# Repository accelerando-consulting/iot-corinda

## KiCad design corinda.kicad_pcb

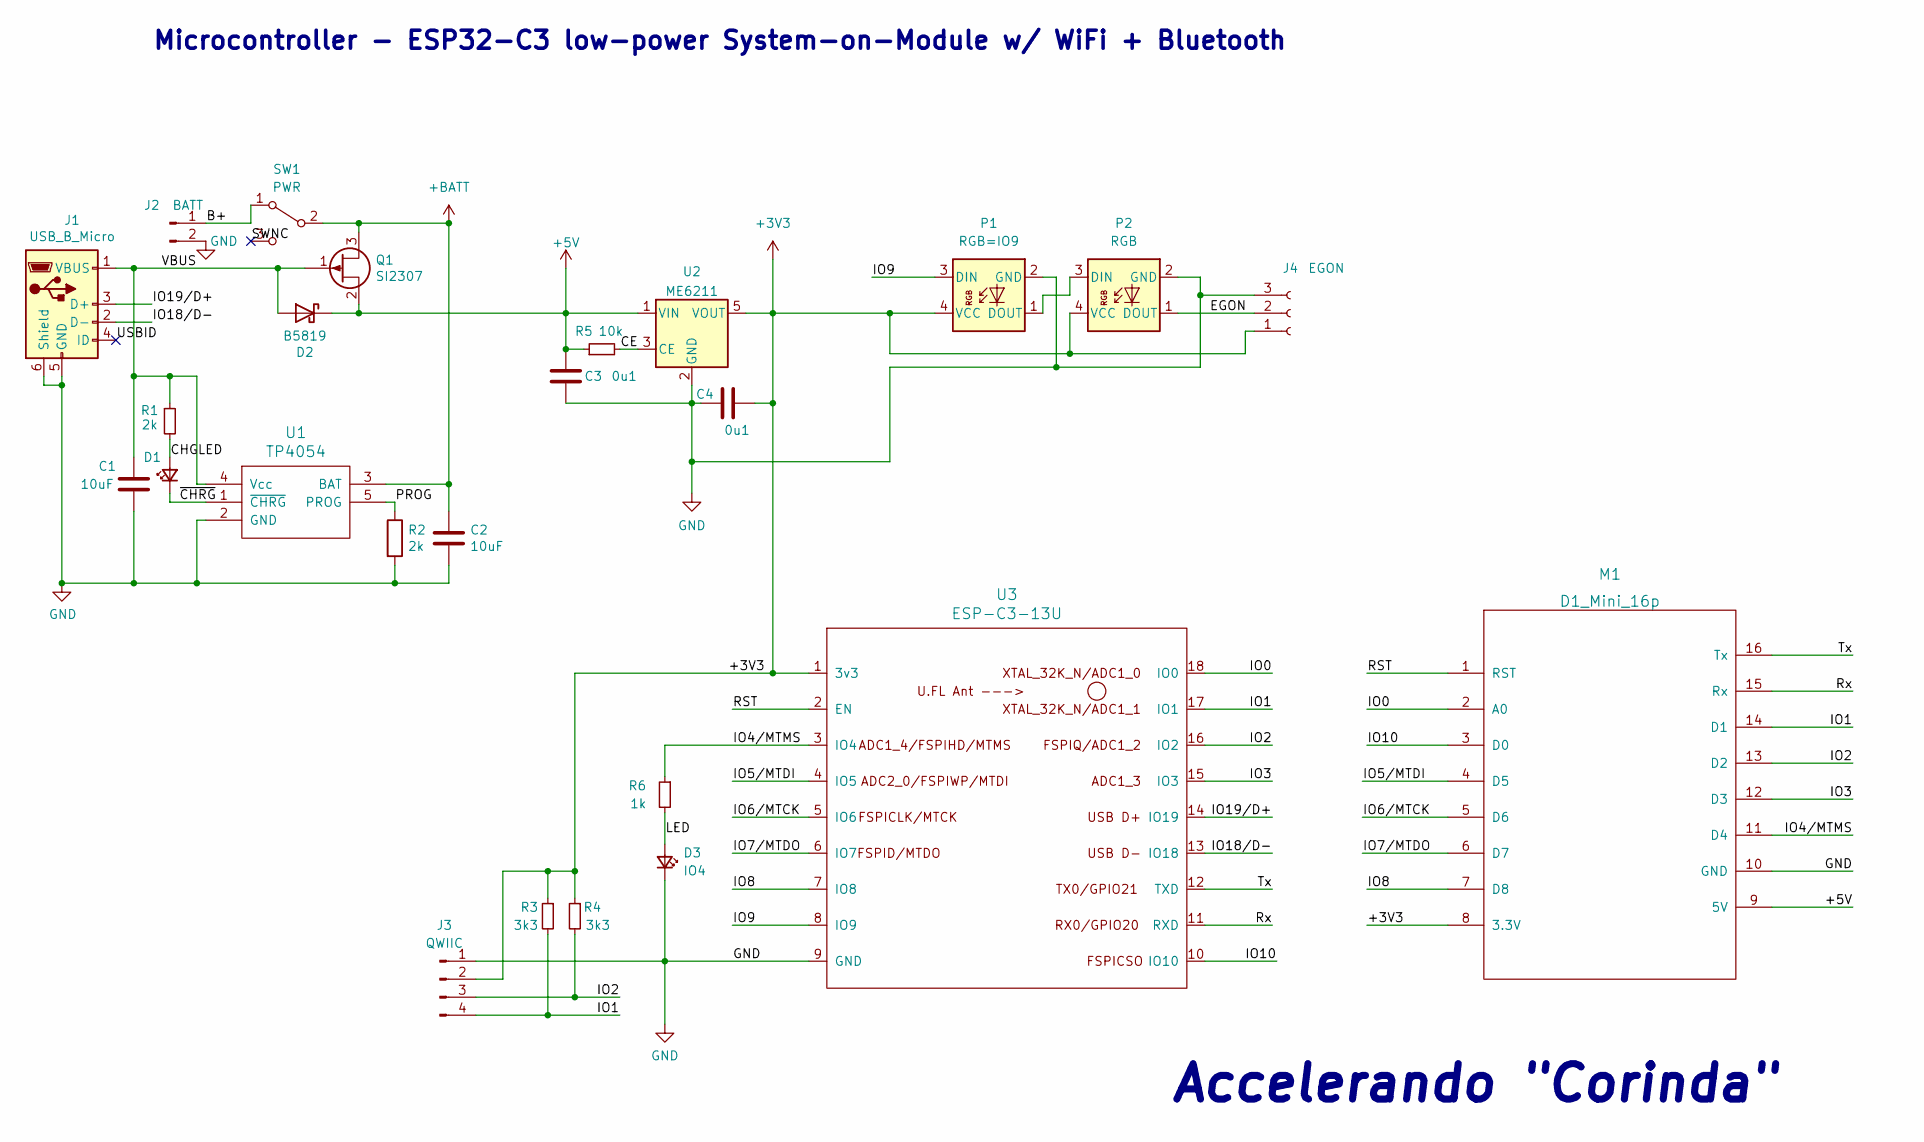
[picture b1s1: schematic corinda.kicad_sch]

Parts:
C1, C2: 10uF; C_0402_1005Metric
C3, C4: 0u1; C_0402_1005Metric
D1: CHG; LED_0402_1005Metric
D2: B5819; D_SOD-123
D3: IO4; LED_0402_1005Metric
J1: USB_B_Micro; USB_Micro_SMD
J2: BATT; JST_GH_SM02B-GHS-TB_1x02-1MP_P1.25mm_Horizontal
J3: QWIIC; JST_SH_SM04B-SRSS-TB_1x04-1MP_P1.00mm_Horizontal
J4: EGON; JST_GH_SM03B-GHS-TB_1x03-1MP_P1.25mm_Horizontal
M1: D1_Mini_16p; wemos-d1-mini-ccw-connectors-only-bigpads
P1: RGB=IO9; LED_WS2812B_PLCC2_0x1_8mm_P1.27mm
P2: RGB; LED_WS2812B_PLCC2_0x1_8mm_P1.27mm
Q1: SI2307; SOT-23
R1, R2: 2k; R_0402_1005Metric
R3, R4: 3k3; R_0402_1005Metric
R5: 10k; R_0402_1005Metric
R6: 1k; R_0402_1005Metric
SW1: PWR; SW_SPDT_PCM12
U1: TP4054; SOT-23-5
U2: ME6211; SOT-23-5
U3: ESP-C3-13U; Ai-Thinker-ESP-C3-13U

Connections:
+3V3: C4.2, J3.2, J4.1, M1.8 (3.3V), P1.4 (VCC), P2.4 (VCC), R3.1, R4.1, U2.5 (VOUT), U3.1 (3v3)
+5V: C3.1, D2.1 (K), M1.9 (5V), Q1.2 (S), R5.1, U2.1 (VIN)
+BATT: C2.1, Q1.3 (D), SW1.2 (B), U1.3 (BAT)
/B+: J2.1, SW1.1 (A)
/CE: R5.2, U2.3 (CE)
/CHGLED: D1.2 (A), R1.2
/EGON: J4.2, P2.1 (DOUT)
/IO0: M1.2 (A0), U3.18 (IO0)
/IO1: J3.4, M1.14 (D1), R3.2, U3.17 (IO1)
/IO2: J3.3, M1.13 (D2), R4.2, U3.16 (IO2)
/IO3: M1.12 (D3), U3.15 (IO3)
/IO4/MTMS: M1.11 (D4), R6.1, U3.3 (IO4)
/IO5/MTDI: M1.4 (D5), U3.4 (IO5)
/IO6/MTCK: M1.5 (D6), U3.5 (IO6)
/IO7/MTDO: M1.6 (D7), U3.6 (IO7)
/IO8: M1.7 (D8), U3.7 (IO8)
/IO9: P1.3 (DIN), U3.8 (IO9)
/IO10: M1.3 (D0), U3.10 (IO10)
/IO18/D-: J1.2 (D-), U3.13 (IO18)
/IO19/D+: J1.3 (D+), U3.14 (IO19)
/LED: D3.2 (A), R6.2
/PROG: R2.1, U1.5 (PROG)
/RST: M1.1 (RST), U3.2 (EN)
/Rx: M1.15 (Rx), U3.11 (RXD)
/SWNC: SW1.3 (C)
/Tx: M1.16 (Tx), U3.12 (TXD)
/USBID: J1.4 (ID)
/VBUS: C1.1, D2.2 (A), J1.1 (VBUS), Q1.1 (G), R1.1, U1.4 (Vcc)
/~CHRG: D1.1 (K), U1.1 (~CHRG)
GND: C1.2, C2.2, C3.2, C4.1, D3.1 (K), J1.5 (GND), J1.6 (Shield), J2.2, J3.1, J4.3, M1.10 (GND), P1.2 (GND), P2.2 (GND), R2.2, U1.2 (GND), U2.2 (GND), U3.9 (GND)
unnamed: P1.1 (DOUT), P2.3 (DIN)

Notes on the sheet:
Accelerando "Corinda"
Microcontroller - ESP32-C3 low-power System-on-Module w/ WiFi + Bluetooth

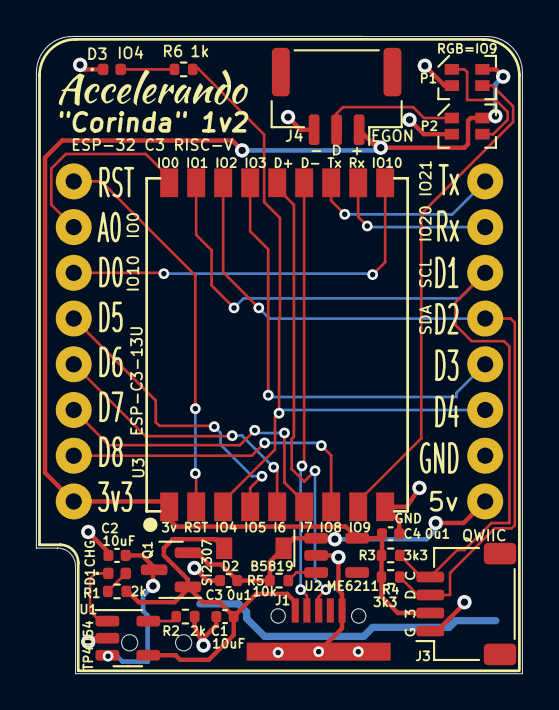
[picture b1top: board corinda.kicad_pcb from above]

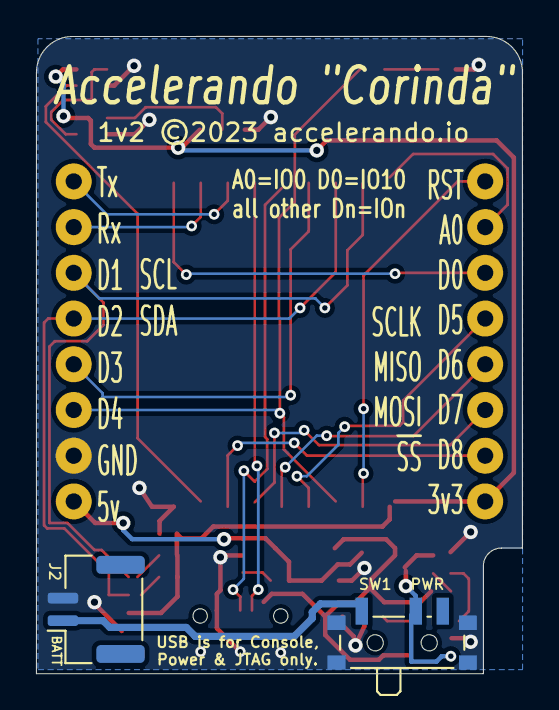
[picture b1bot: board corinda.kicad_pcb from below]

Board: 2 copper layers, 27.0 x 35.4 mm, 25 parts (2 on the bottom side), 29 nets.

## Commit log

2022-03-18 Corinda 1v0
2023-08-22 Corinda 1v1
2023-08-22 Add production files
2024-05-21 Version 1.2 - battery charger

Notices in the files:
corinda.kicad_pcb:
1v2 ©2023 accelerando.io
